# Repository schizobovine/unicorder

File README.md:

# unicorder
Play on the device of Trek fame, just a little bit less capable (only designed to handle a single sensor).

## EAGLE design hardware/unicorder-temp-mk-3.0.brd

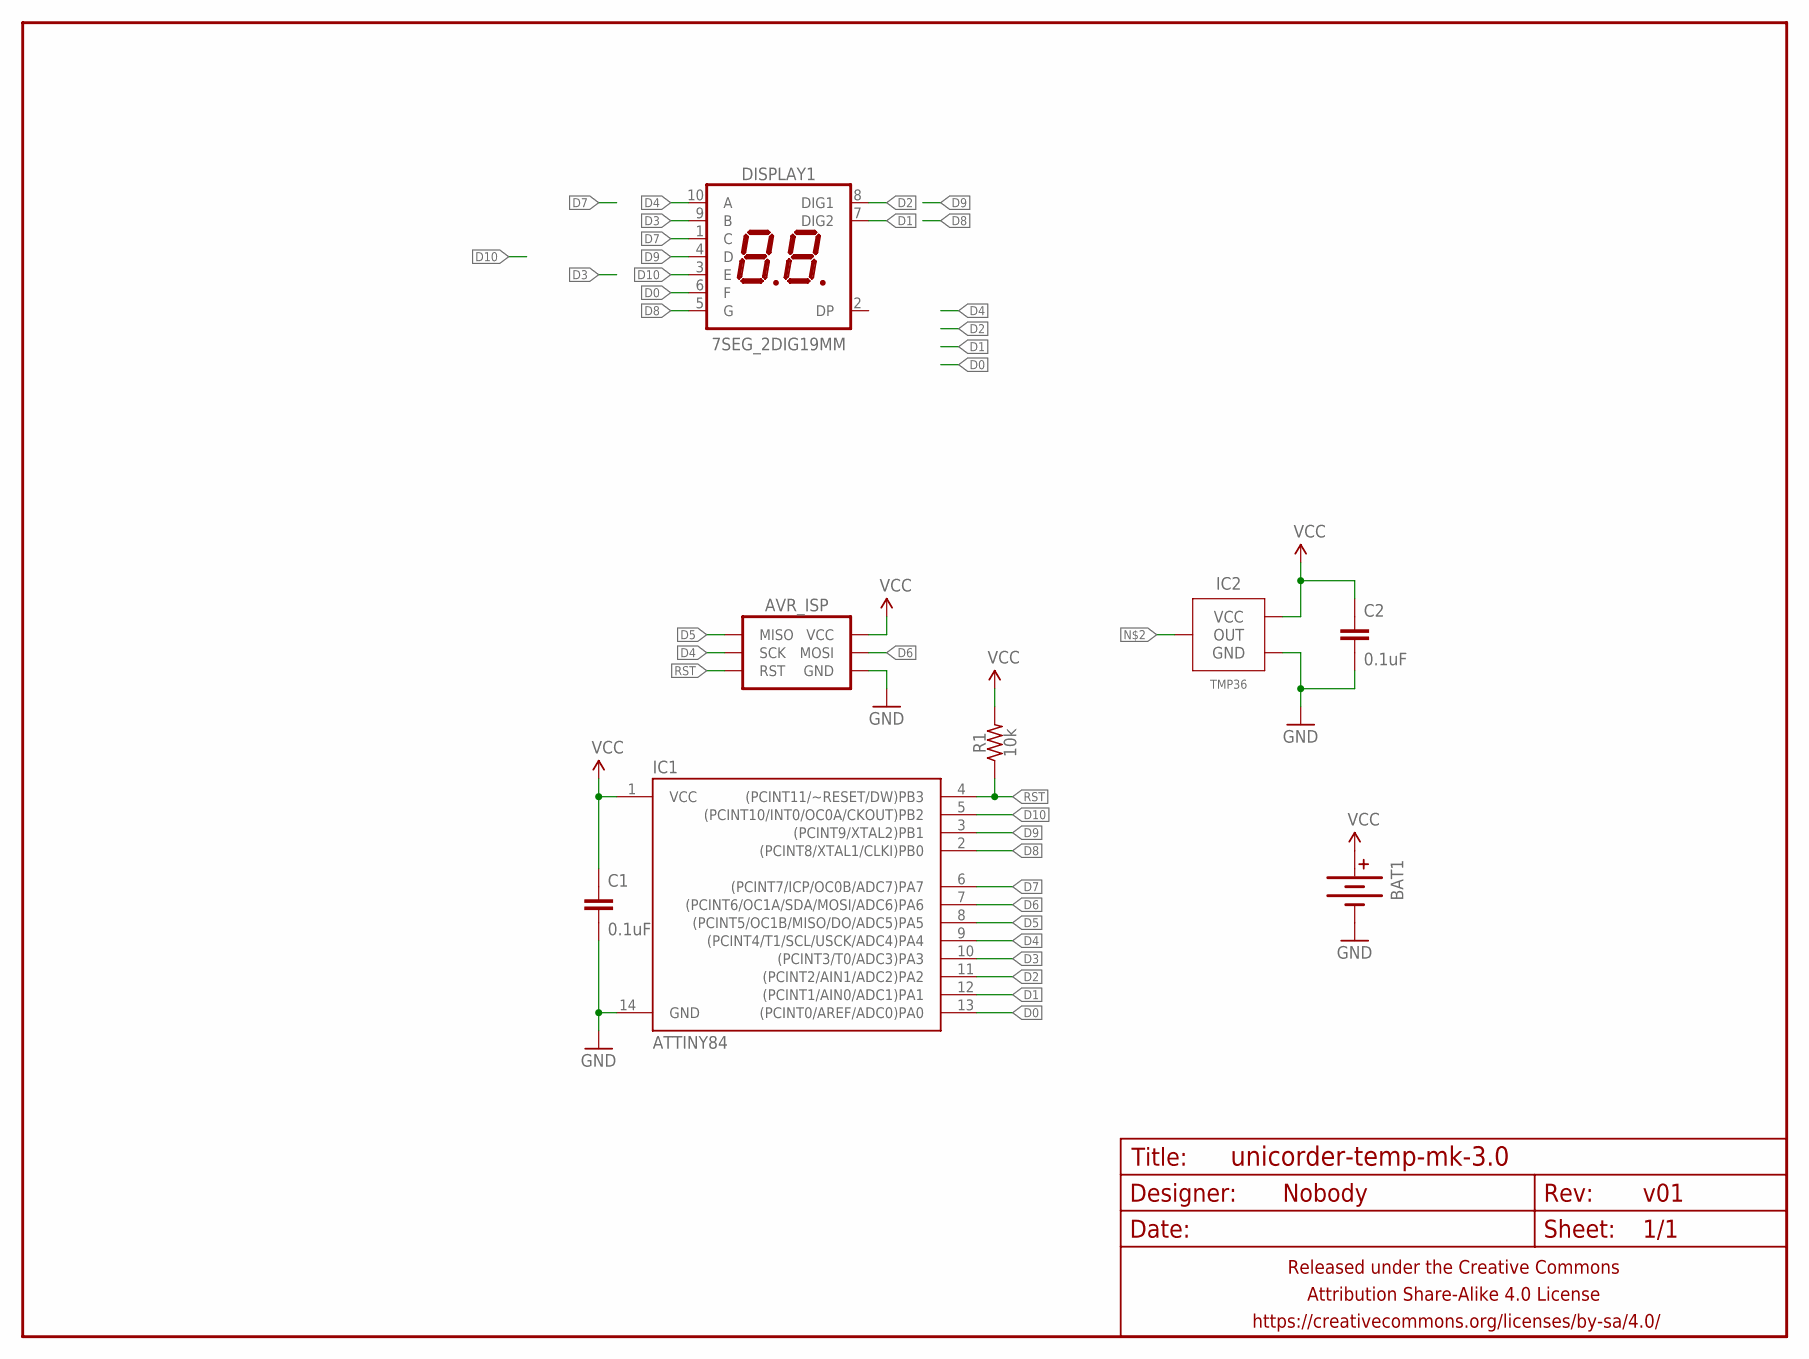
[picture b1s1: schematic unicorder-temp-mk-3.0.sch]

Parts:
AVR_ISP: AVR_SPI_PRG_6SMD_TEST_POINTS; 2X3_SMD_TEST_POINTS
BAT1: BATTERY20PTH_TOPLOAD; BATTCON_20MM_PTH_TOPLOAD
C1: 0.1uF; C0805
C2: 0.1uF; C025-024X044
DISPLAY1: 7SEG_2DIG19MM; 7SEG_2DIG_19MM
FRAME1: FRAME-LETTERNO_PACKAGE; DUMMY
IC1: ATTINY84; SO14
IC2: TMP36; TO-92-AMMO
R1: 10k; R0805

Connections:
D0: DISPLAY1.6 (F), IC1.13 ((PCINT0/AREF/ADC0)PA0)
D1: DISPLAY1.7 (DIG2), IC1.12 ((PCINT1/AIN0/ADC1)PA1)
D2: DISPLAY1.8 (DIG1), IC1.11 ((PCINT2/AIN1/ADC2)PA2)
D3: DISPLAY1.9 (B), IC1.10 ((PCINT3/T0/ADC3)PA3)
D4: AVR_ISP.3 (SCK), DISPLAY1.10 (A), IC1.9 ((PCINT4/T1/SCL/USCK/ADC4)PA4)
D5: AVR_ISP.1 (MISO), IC1.8 ((PCINT5/OC1B/MISO/DO/ADC5)PA5)
D6: AVR_ISP.4 (MOSI), IC1.7 ((PCINT6/OC1A/SDA/MOSI/ADC6)PA6)
D7: DISPLAY1.1 (C), IC1.6 ((PCINT7/ICP/OC0B/ADC7)PA7)
D8: DISPLAY1.5 (G), IC1.2 ((PCINT8/XTAL1/CLKI)PB0)
D9: DISPLAY1.4 (D), IC1.3 ((PCINT9/XTAL2)PB1)
D10: DISPLAY1.3 (E), IC1.5 ((PCINT10/INT0/OC0A/CKOUT)PB2)
GND: AVR_ISP.6 (GND), BAT1.-, C1.2, C2.2, IC1.14 (GND), IC2.3 (GND)
RST: AVR_ISP.5 (RST), IC1.4 ((PCINT11/~RESET/DW)PB3), R1.1
VCC: AVR_ISP.2 (VCC), BAT1.+, C1.1, C2.1, IC1.1 (VCC), IC2.1 (VCC), R1.2

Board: 2 copper layers, 9 parts (6 on the bottom side), 14 nets, no tracks yet.

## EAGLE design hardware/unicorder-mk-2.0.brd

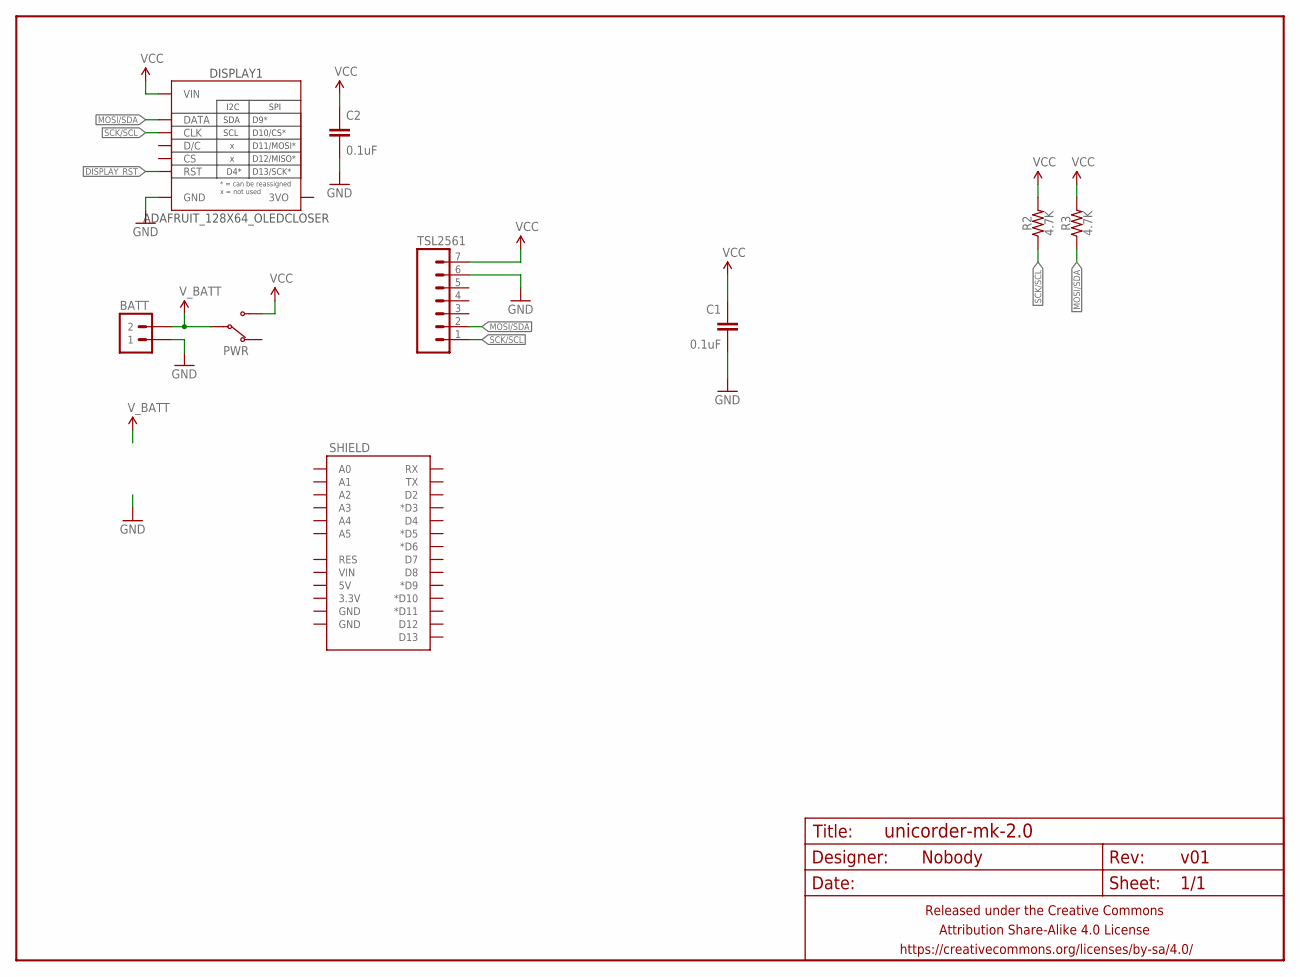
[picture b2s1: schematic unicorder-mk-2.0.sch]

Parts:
BATT: M02JST-PTH-VERT; JST-2-PH-VERT-PTH
C1, C2: 0.1uF; C025-024X044
DISPLAY1: ADAFRUIT_128X64_OLEDCLOSER; ADAFRUIT_128X64_OLED_CLOSER
FRAME1: FRAME-LETTERNO_PACKAGE; DUMMY
PWR: SWITCH-SPDTPTH-RA-2MM; SPDT-RA-2MM
R2, R3: 4.7K; RESISTOR-AXIAL-PTH-5.08MM
SHIELD: ARDUINO_SHIELD_SMALLER; ARDUINO_SHIELD_NOOUTLINE_INSIDE_SMALLER
TSL2561: M07PTH-SLIMASS; 1X07_PTH_SLIMASS

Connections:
DISPLAY_RST: DISPLAY1.RST
GND: BATT.1, C1.2, C2.2, DISPLAY1.GND, TSL2561.6
MOSI/SDA: DISPLAY1.DATA, R3.P$1 (1), TSL2561.2
SCK/SCL: DISPLAY1.CLK, R2.P$1 (1), TSL2561.1
VCC: C1.1, C2.1, DISPLAY1.VIN, PWR.3 (NO), R2.P$2 (2), R3.P$2 (2), TSL2561.7
V_BATT: BATT.2, PWR.2 (COM)

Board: 2 copper layers, 10 parts (1 on the bottom side), 5 nets, no tracks yet.

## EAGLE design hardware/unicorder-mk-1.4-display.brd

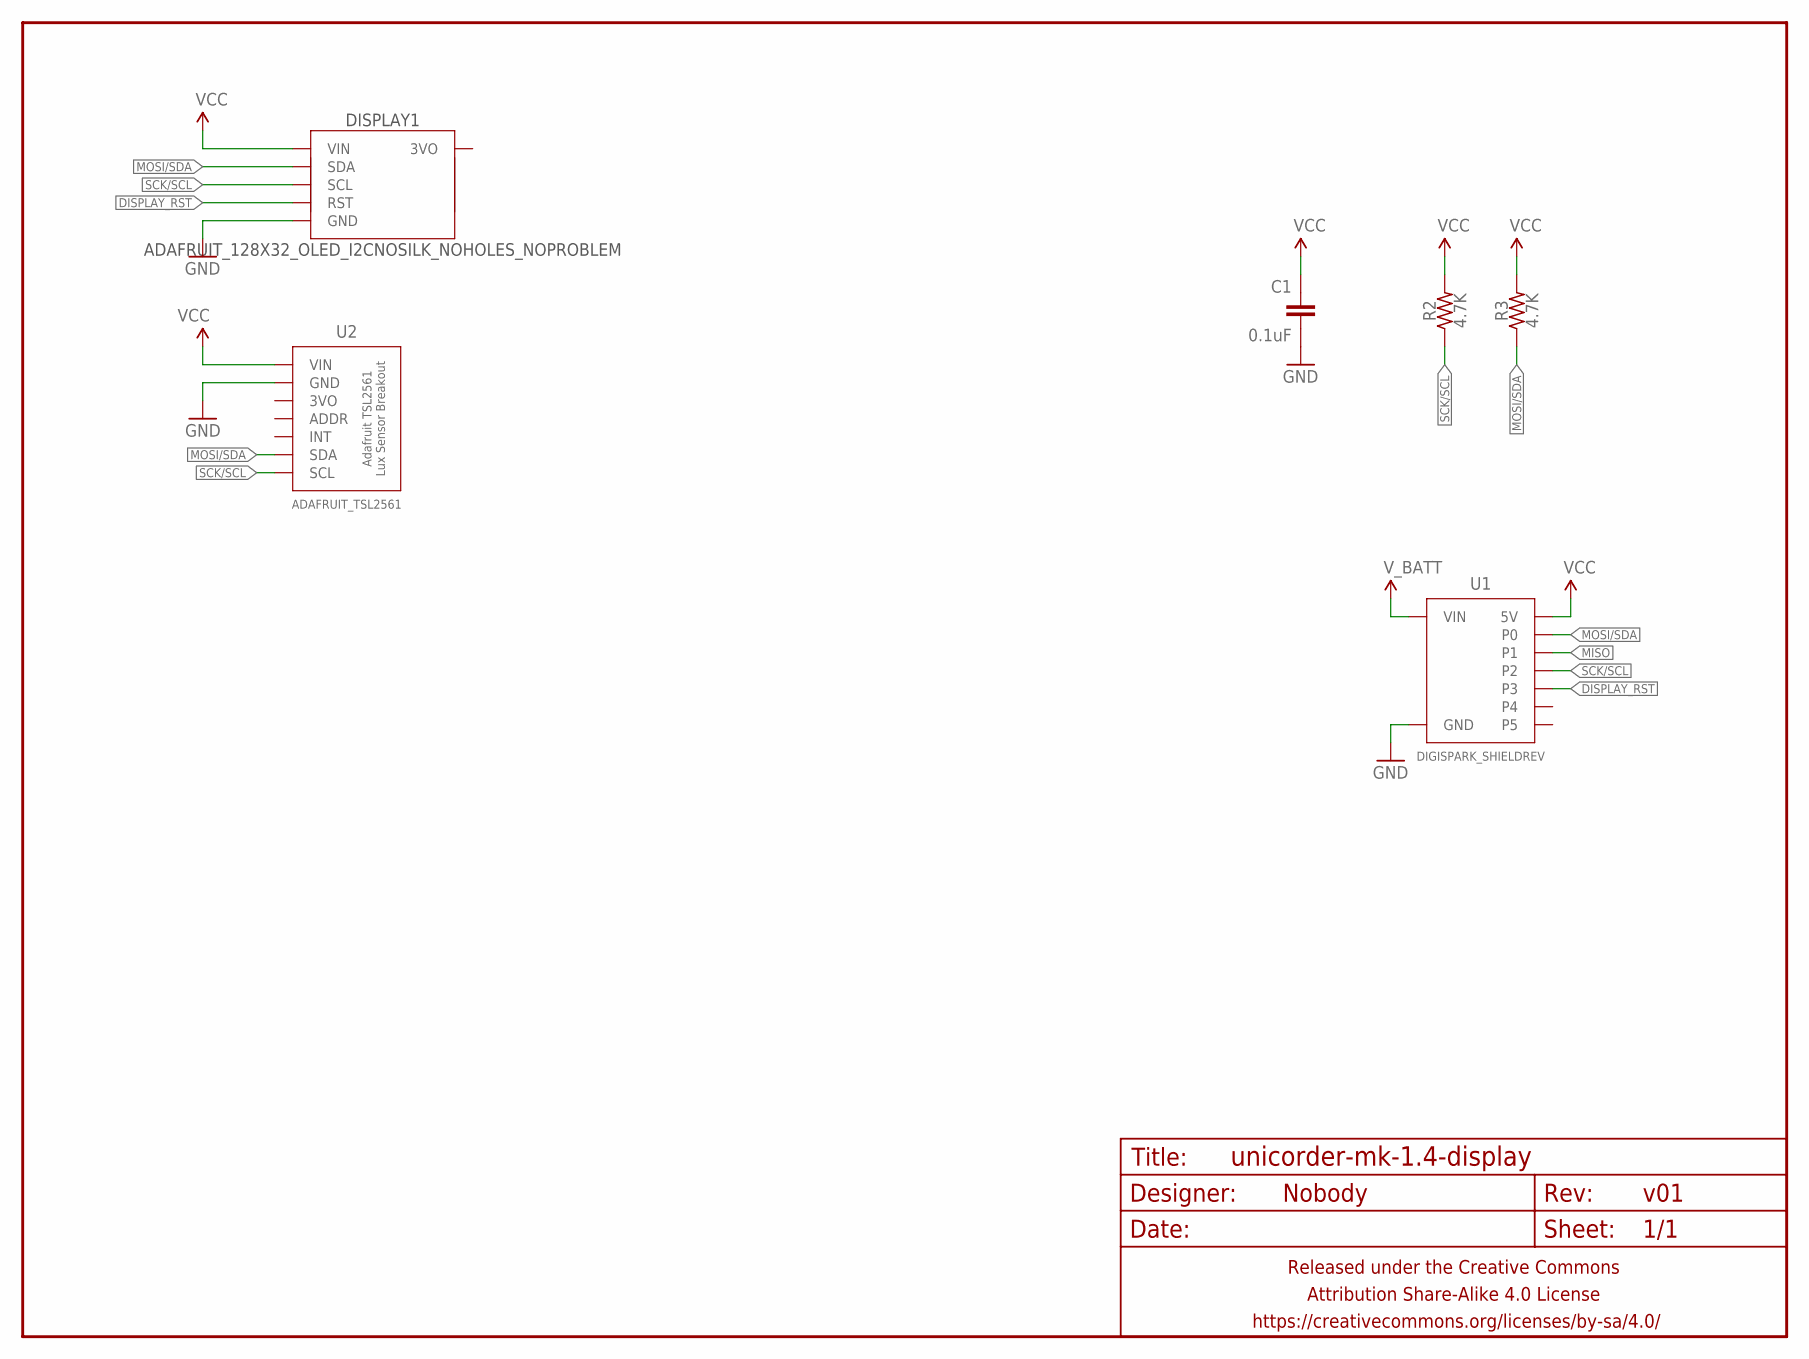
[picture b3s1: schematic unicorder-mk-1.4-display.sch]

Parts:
C1: 0.1uF; C025-024X044
DISPLAY1: ADAFRUIT_128X32_OLED_I2CNOSILK_NOHOLES_NOPROBLEM; ADAFRUIT_128X32_OLED_I2C_CLOSER_NS
FRAME1: FRAME-LETTERNO_PACKAGE; DUMMY
R2, R3: 4.7K; RESISTOR-AXIAL-PTH-7.62MM
U1: DIGISPARK_SHIELDREV; DIGISPARK_SHIELD_REV
U2: ADAFRUIT_TSL2561

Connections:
DISPLAY_RST: DISPLAY1.RST, U1.P3
GND: C1.2, DISPLAY1.GND, U1.GND, U2.GND
MISO: U1.P1
MOSI/SDA: DISPLAY1.SDA, R3.P$1 (1), U1.P0, U2.SDA
SCK/SCL: DISPLAY1.SCL, R2.P$1 (1), U1.P2, U2.SCL
VCC: C1.1, DISPLAY1.VIN, R2.P$2 (2), R3.P$2 (2), U1.5V, U2.VIN
V_BATT: U1.VIN

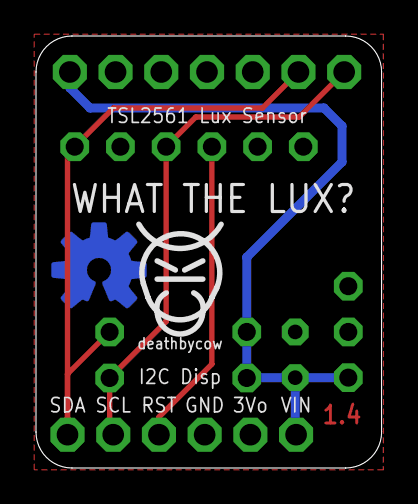
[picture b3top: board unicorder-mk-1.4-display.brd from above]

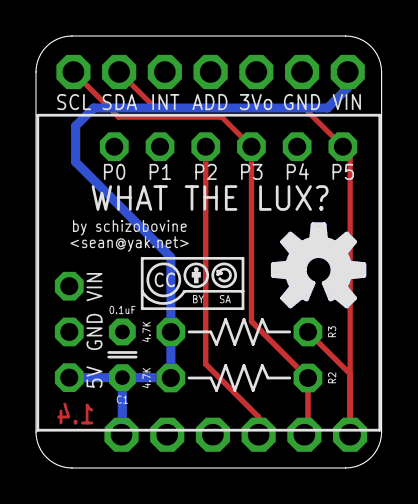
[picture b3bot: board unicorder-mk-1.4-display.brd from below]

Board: 2 copper layers, 19.2 x 24.0 mm, 10 parts (6 on the bottom side), 5 nets.

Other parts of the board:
U$1: CC-BY-SA-4.0-NO-URL
U$2: COW_SMALL
U$3: OSHWLOGO_TOP_0.2

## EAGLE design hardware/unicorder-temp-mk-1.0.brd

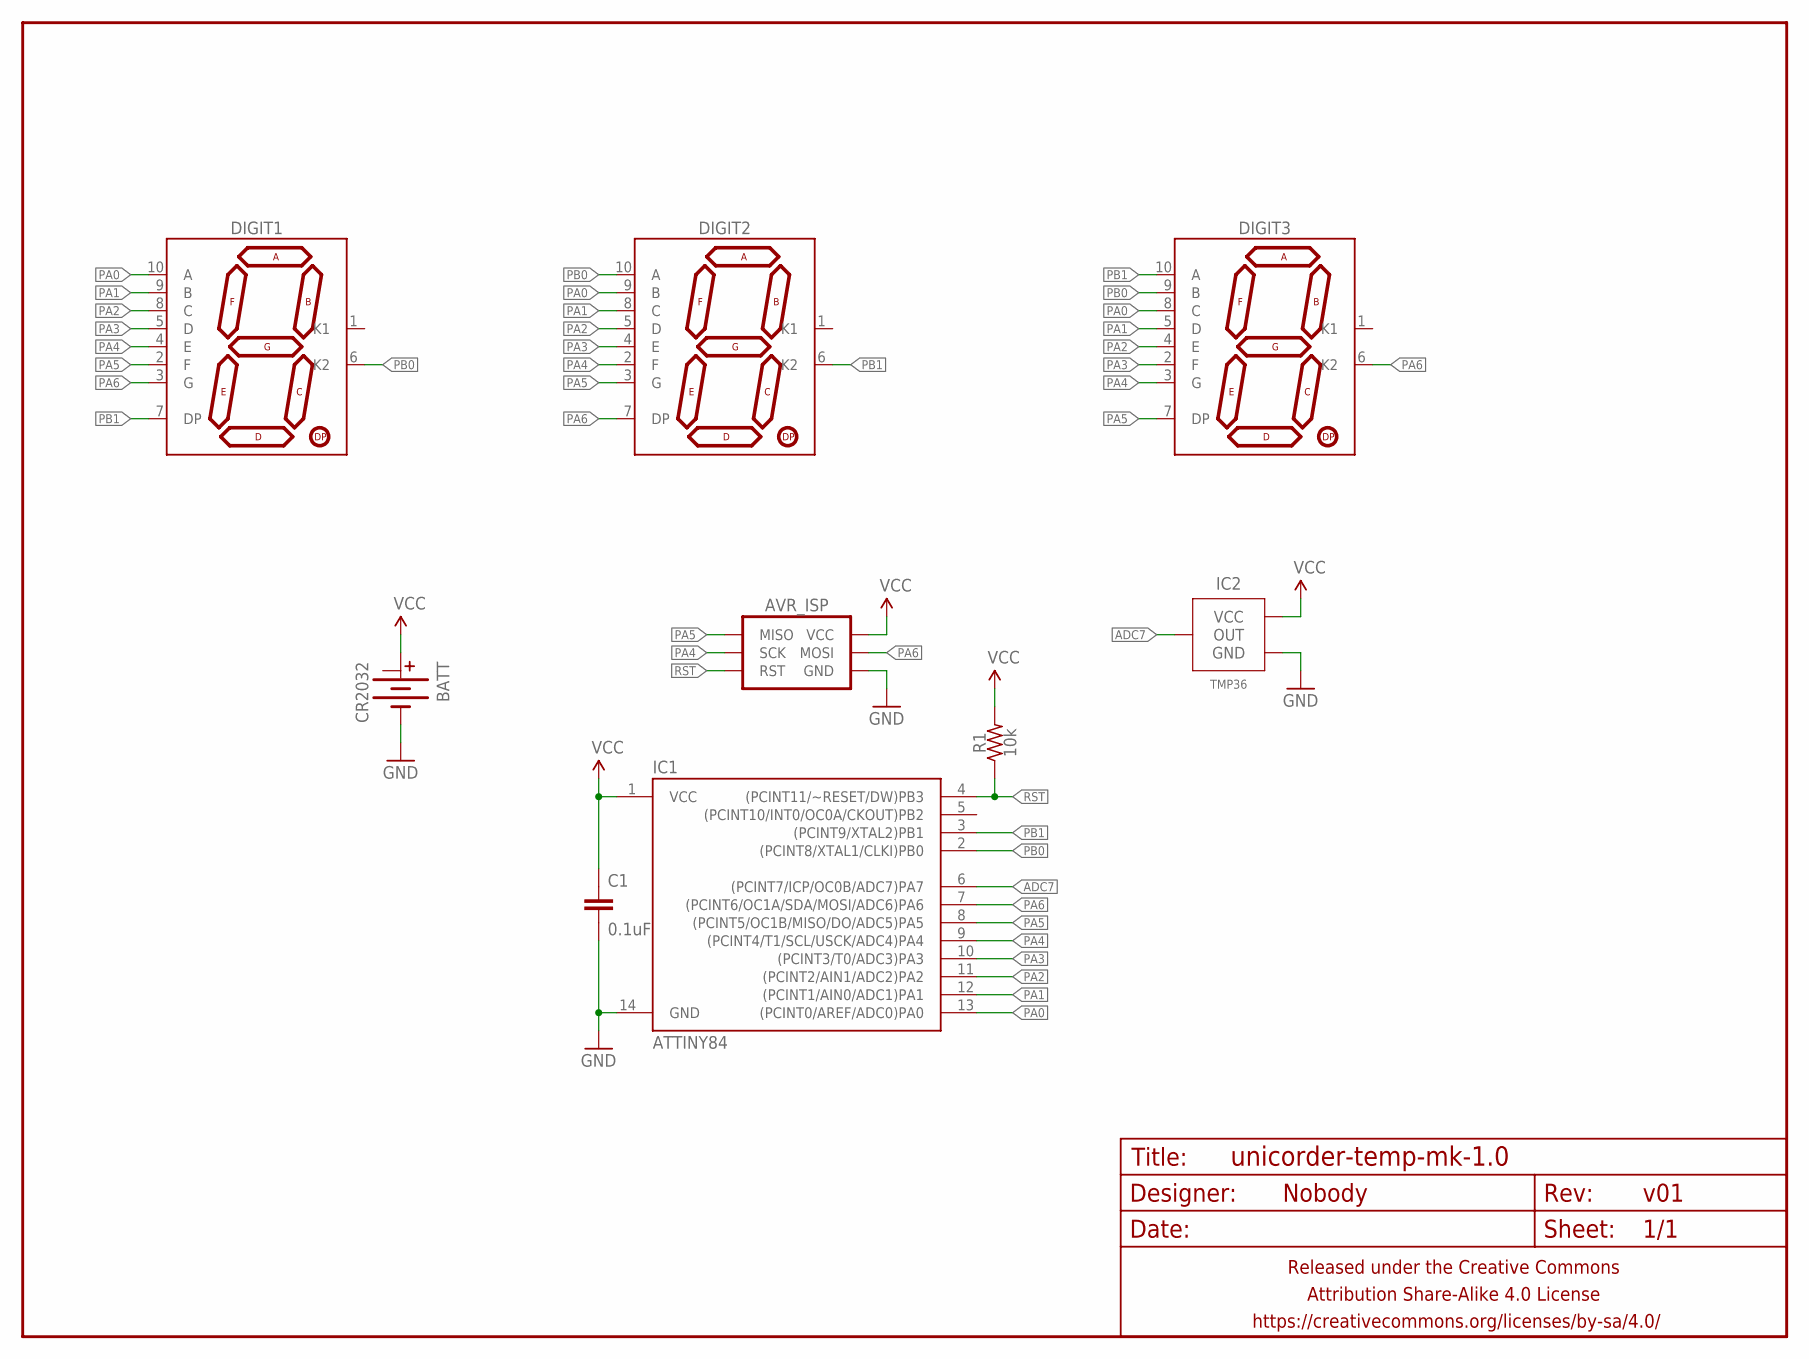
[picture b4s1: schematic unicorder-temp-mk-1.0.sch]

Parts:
AVR_ISP: AVR_SPI_PRG_6PTH; 2X3
BATT: CR2032; BATTCON_20MM_MINE
C1: 0.1uF; C025-024X044
DIGIT1, DIGIT2, DIGIT3: 7SEG_1DIGPTH-10MM; 7SEG_1DIG_10MM
FRAME1: FRAME-LETTERNO_PACKAGE; DUMMY
IC1: ATTINY84; DIL14
IC2: TMP36; TO-92-AMMO
R1: 10k; RESISTOR-AXIAL-PTH-7.62MM

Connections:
ADC7: IC1.6 ((PCINT7/ICP/OC0B/ADC7)PA7), IC2.2 (OUT)
GND: AVR_ISP.6 (GND), BATT.BOTTOM (-), C1.2, IC1.14 (GND), IC2.3 (GND)
PA0: DIGIT1.10 (A), DIGIT2.9 (B), DIGIT3.8 (C), IC1.13 ((PCINT0/AREF/ADC0)PA0)
PA1: DIGIT1.9 (B), DIGIT2.8 (C), DIGIT3.5 (D), IC1.12 ((PCINT1/AIN0/ADC1)PA1)
PA2: DIGIT1.8 (C), DIGIT2.5 (D), DIGIT3.4 (E), IC1.11 ((PCINT2/AIN1/ADC2)PA2)
PA3: DIGIT1.5 (D), DIGIT2.4 (E), DIGIT3.2 (F), IC1.10 ((PCINT3/T0/ADC3)PA3)
PA4: AVR_ISP.3 (SCK), DIGIT1.4 (E), DIGIT2.2 (F), DIGIT3.3 (G), IC1.9 ((PCINT4/T1/SCL/USCK/ADC4)PA4)
PA5: AVR_ISP.1 (MISO), DIGIT1.2 (F), DIGIT2.3 (G), DIGIT3.7 (DP), IC1.8 ((PCINT5/OC1B/MISO/DO/ADC5)PA5)
PA6: AVR_ISP.4 (MOSI), DIGIT1.3 (G), DIGIT2.7 (DP), DIGIT3.6 (K2), IC1.7 ((PCINT6/OC1A/SDA/MOSI/ADC6)PA6)
PB0: DIGIT1.6 (K2), DIGIT2.10 (A), DIGIT3.9 (B), IC1.2 ((PCINT8/XTAL1/CLKI)PB0)
PB1: DIGIT1.7 (DP), DIGIT2.6 (K2), DIGIT3.10 (A), IC1.3 ((PCINT9/XTAL2)PB1)
RST: AVR_ISP.5 (RST), IC1.4 ((PCINT11/~RESET/DW)PB3), R1.P$1 (1)
VCC: AVR_ISP.2 (VCC), BATT.TOP@1 (+), C1.1, IC1.1 (VCC), IC2.1 (VCC), R1.P$2 (2)

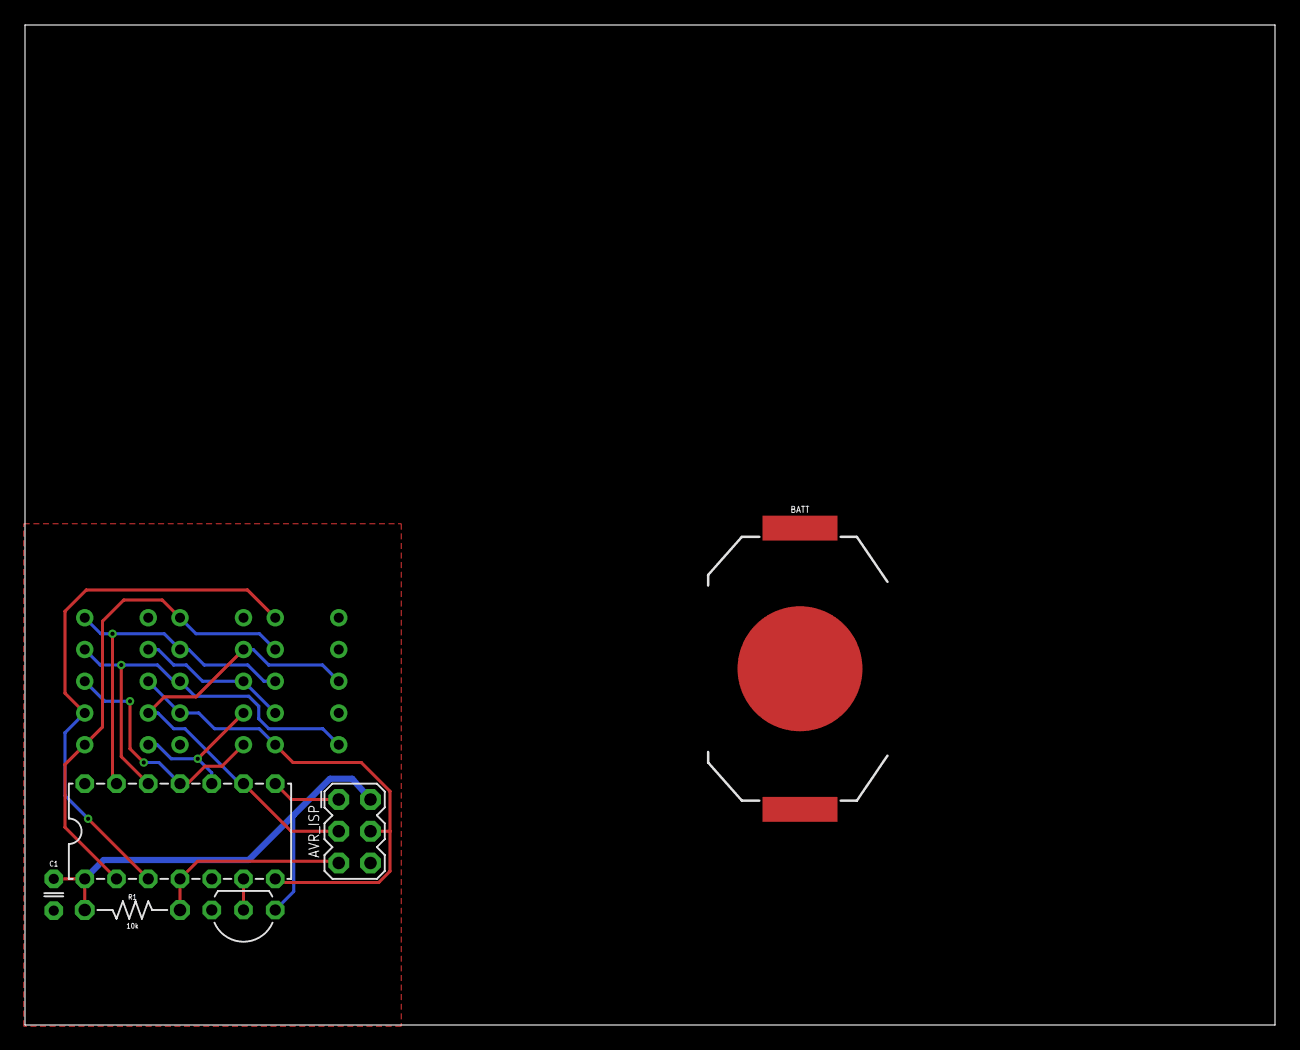
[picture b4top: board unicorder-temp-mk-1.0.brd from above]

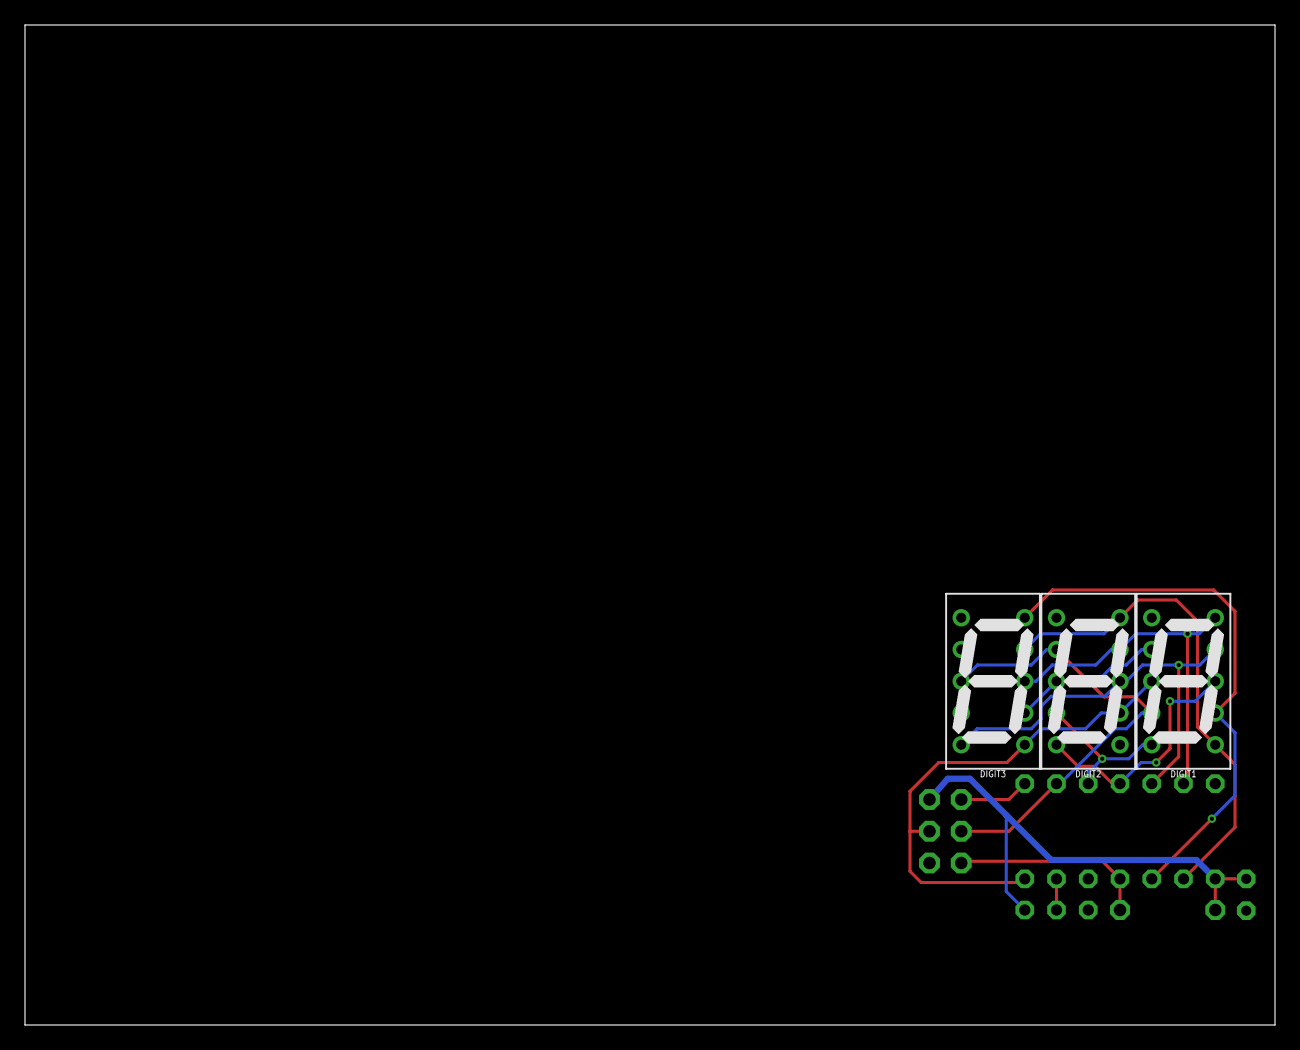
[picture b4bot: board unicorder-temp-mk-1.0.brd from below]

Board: 2 copper layers, 100.0 x 80.0 mm, 10 parts (3 on the bottom side), 13 nets.

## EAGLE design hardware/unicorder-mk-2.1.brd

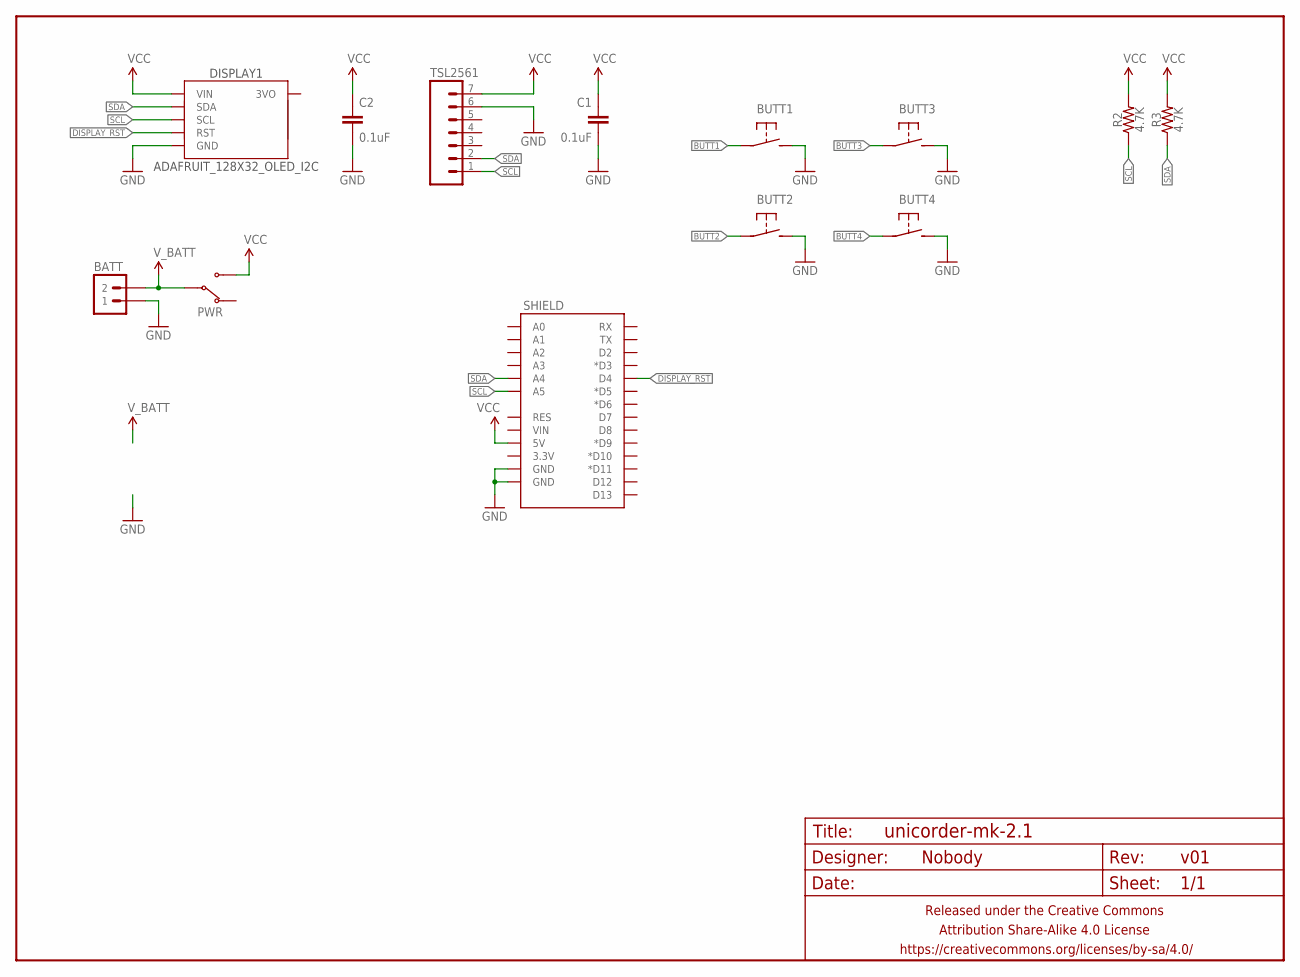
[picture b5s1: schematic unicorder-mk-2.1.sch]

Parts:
BATT: M02JST-PTH-VERT; JST-2-PH-VERT-PTH
BUTT1, BUTT2, BUTT3, BUTT4: SPST-NO-TACT6MM-PTH-SMALL-PADS; DTS-6-SMALL-PADS
C1, C2: 0.1uF; C025-024X044
DISPLAY1: ADAFRUIT_128X32_OLED_I2C; ADAFRUIT_128X32_OLED_I2C_CLOSER
FRAME1: FRAME-LETTERNO_PACKAGE; DUMMY
PWR: SWITCH-SPDTPTH-VERT-2.54MM; SWITCH-SPDT
R2, R3: 4.7K; RESISTOR-AXIAL-PTH-6.35MM
SHIELD: ARDUINO_SHIELD_SMALLER; ARDUINO_SHIELD_NOOUTLINE_INSIDE_SMALLER
TSL2561: M07PTH-SLIMASS; 1X07_PTH_SLIMASS

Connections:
BUTT1: BUTT1.1, BUTT1.2 (1)
BUTT2: BUTT2.1, BUTT2.2 (1)
BUTT3: BUTT3.1, BUTT3.2 (1)
BUTT4: BUTT4.1, BUTT4.2 (1)
DISPLAY_RST: DISPLAY1.RST, SHIELD.D4
GND: BATT.1, BUTT1.3 (2), BUTT1.4 (2), BUTT2.3 (2), BUTT2.4 (2), BUTT3.3 (2), BUTT3.4 (2), BUTT4.3 (2), BUTT4.4 (2), C1.2, C2.2, DISPLAY1.GND, SHIELD.GND@0 (GND), SHIELD.GND@1 (GND), TSL2561.6
SCL: DISPLAY1.SCL, R2.P$1 (1), SHIELD.A5, TSL2561.1
SDA: DISPLAY1.SDA, R3.P$1 (1), SHIELD.A4, TSL2561.2
VCC: C1.1, C2.1, DISPLAY1.VIN, PWR.3 (NO), R2.P$2 (2), R3.P$2 (2), SHIELD.5V, TSL2561.7
V_BATT: BATT.2, PWR.2 (COM)

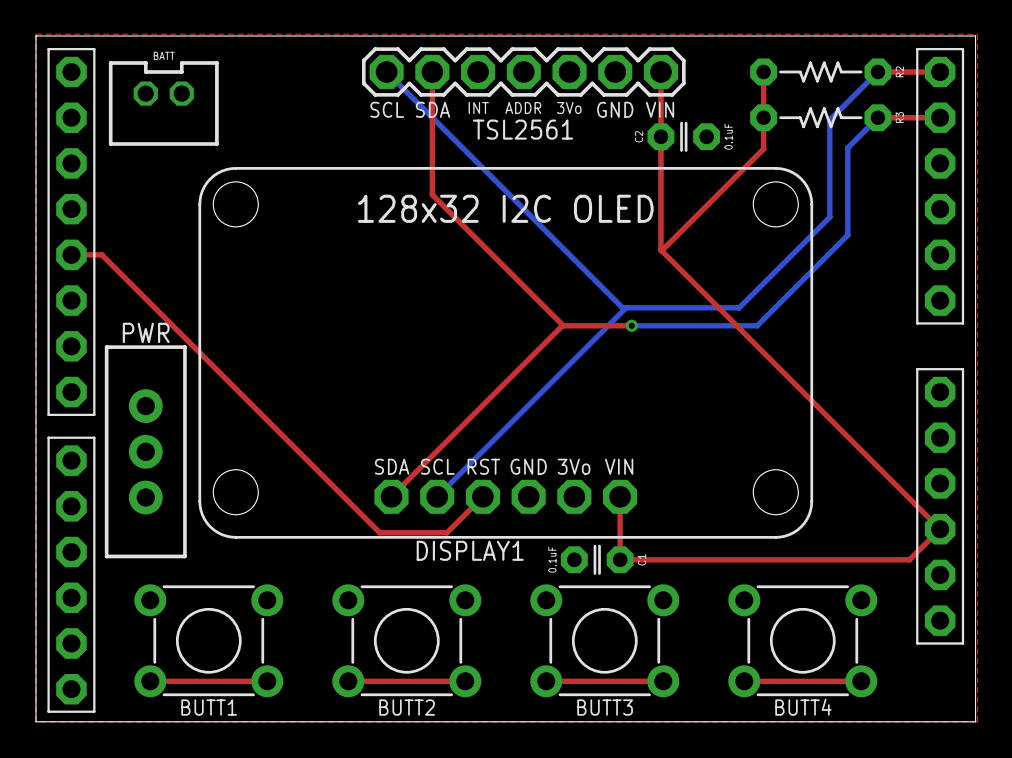
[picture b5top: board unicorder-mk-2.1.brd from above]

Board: 2 copper layers, 52.2 x 38.1 mm, 14 parts (0 on the bottom side), 10 nets.

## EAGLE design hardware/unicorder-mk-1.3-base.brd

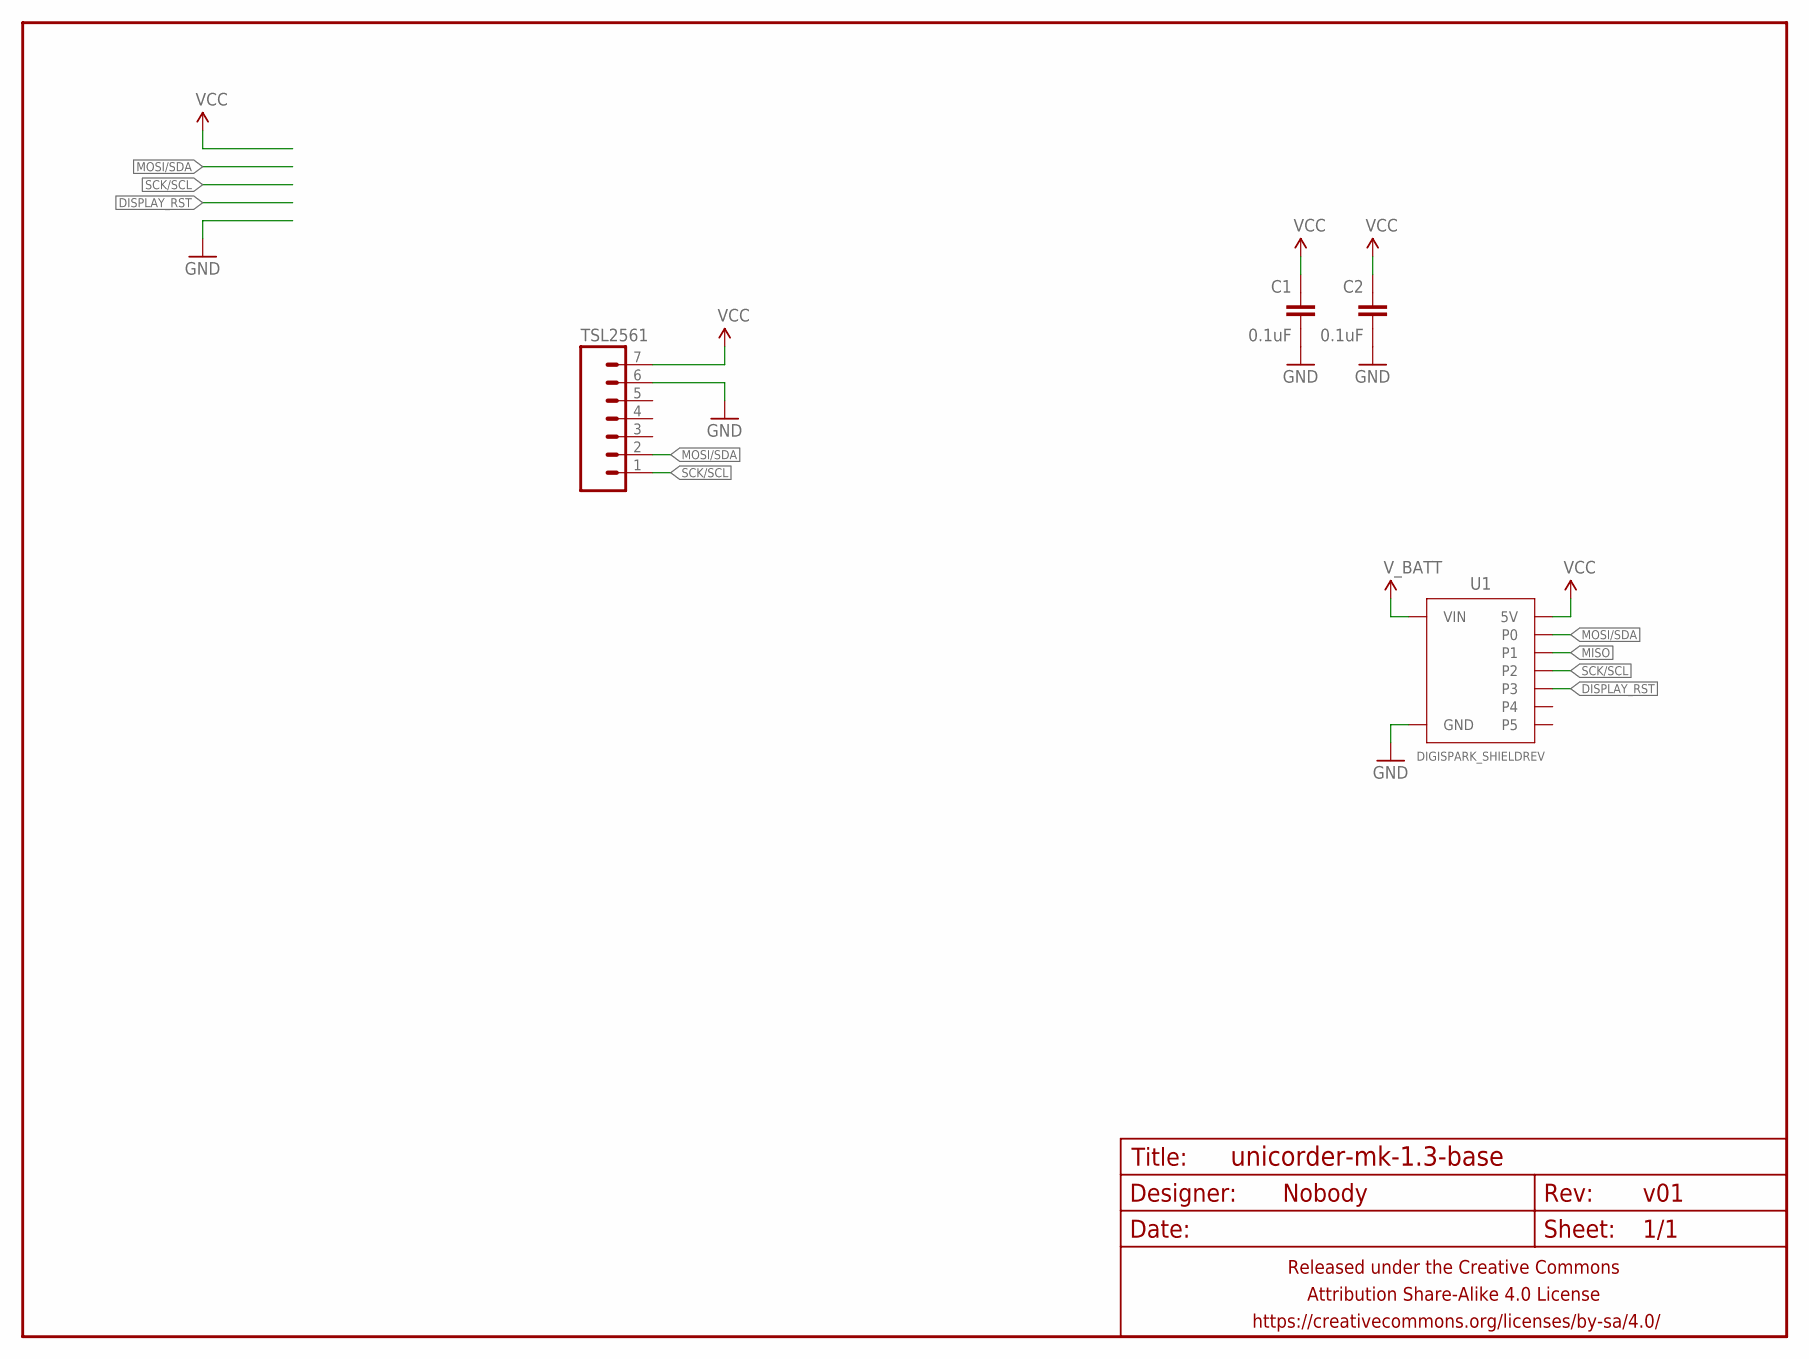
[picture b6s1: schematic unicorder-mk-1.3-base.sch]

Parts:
C1, C2: 0.1uF; C025-024X044
FRAME1: FRAME-LETTERNO_PACKAGE; DUMMY
TSL2561: M07PTH-SLIMASS; 1X07_PTH_SLIMASS
U1: DIGISPARK_SHIELDREV; DIGISPARK_SHIELD_REV

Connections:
DISPLAY_RST: U1.P3
GND: C1.2, C2.2, TSL2561.6, U1.GND
MISO: U1.P1
MOSI/SDA: TSL2561.2, U1.P0
SCK/SCL: TSL2561.1, U1.P2
VCC: C1.1, C2.1, TSL2561.7, U1.5V
V_BATT: U1.VIN

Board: 2 copper layers, 5 parts (4 on the bottom side), 4 nets, no tracks yet.

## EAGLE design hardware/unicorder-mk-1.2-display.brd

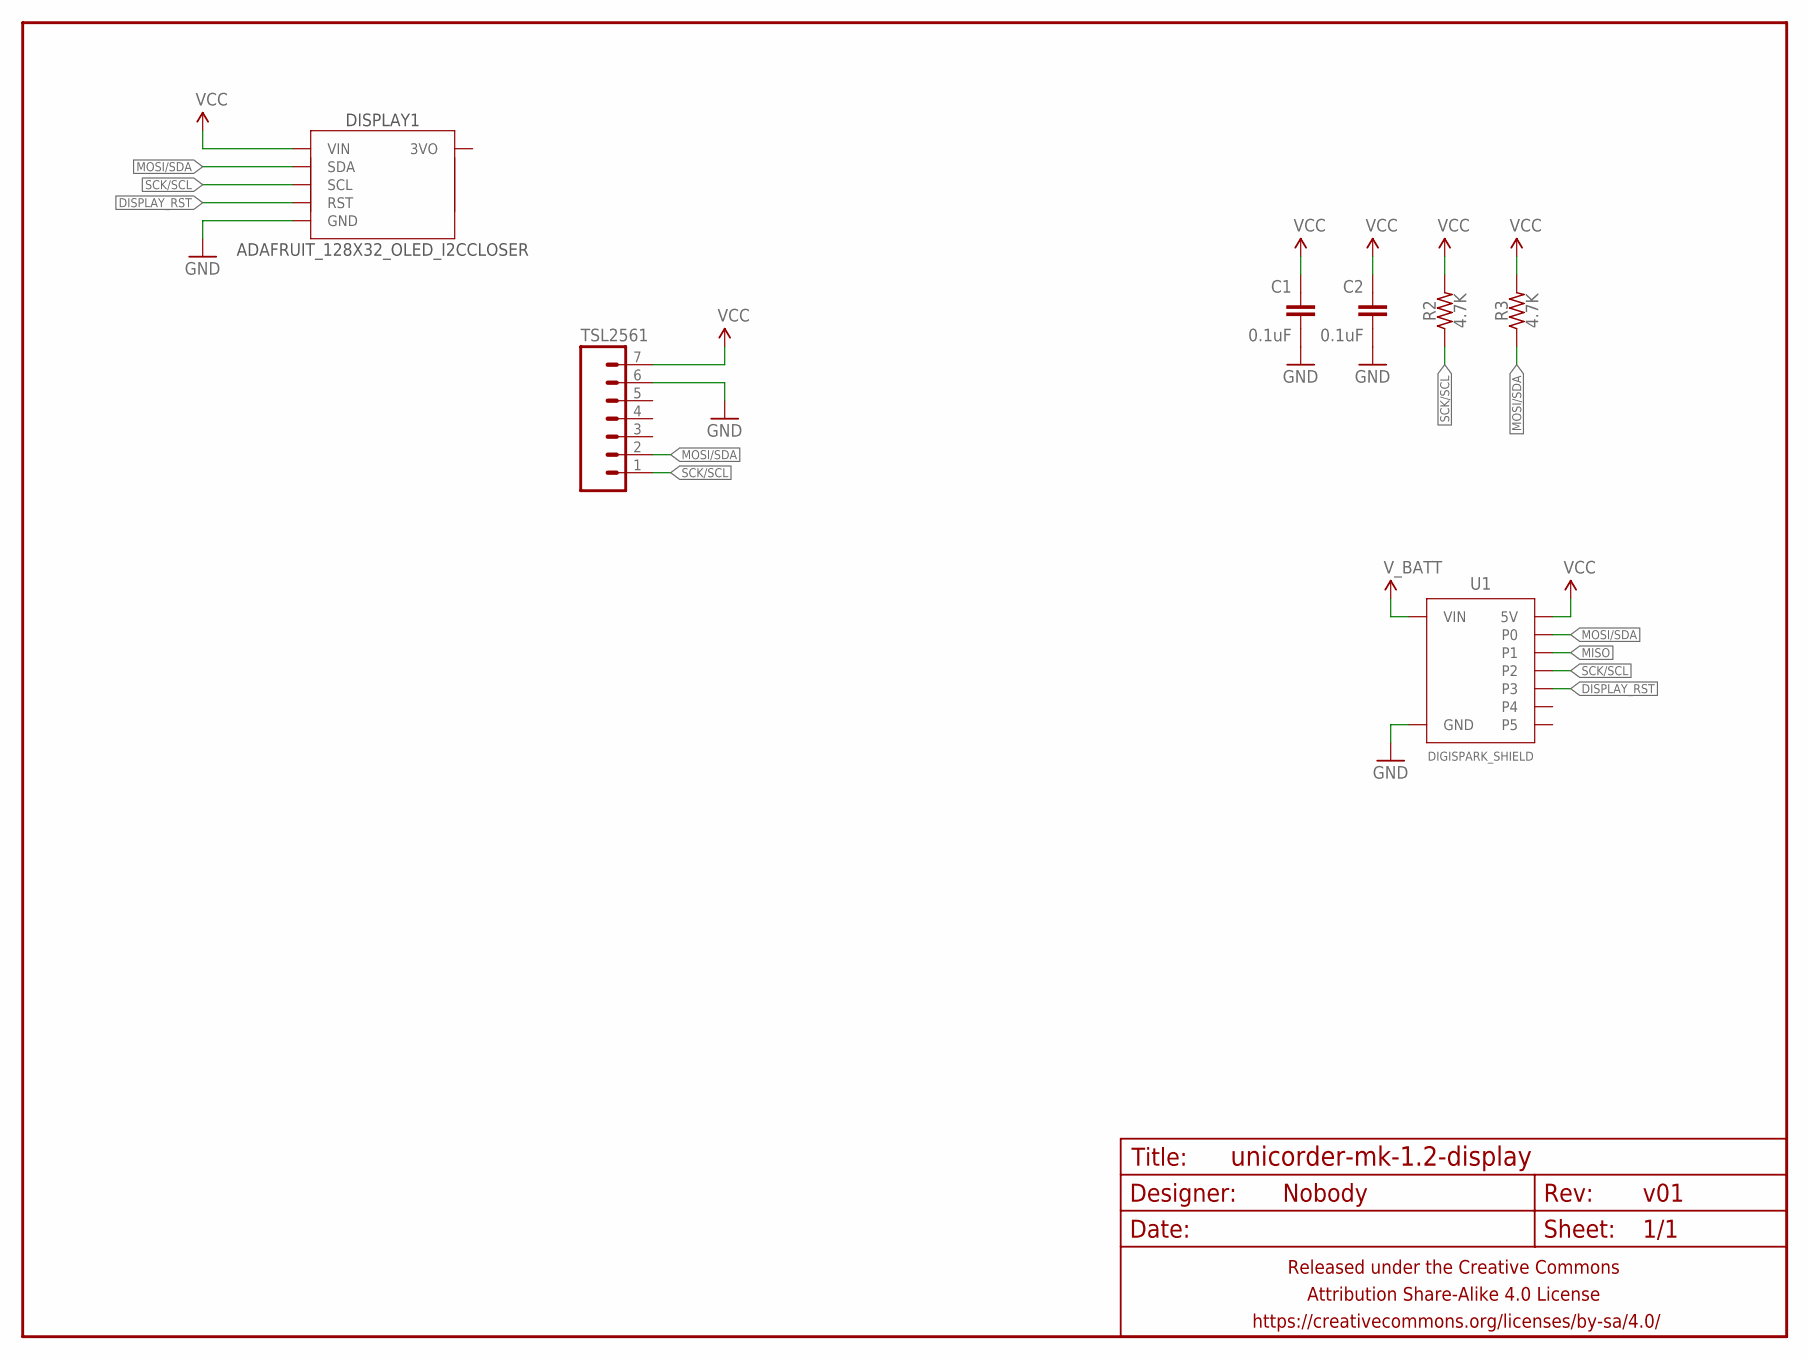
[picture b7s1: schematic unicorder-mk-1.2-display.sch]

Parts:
C1, C2: 0.1uF; C025-024X044
DISPLAY1: ADAFRUIT_128X32_OLED_I2CCLOSER; ADAFRUIT_128X32_OLED_I2C_CLOSER
FRAME1: FRAME-LETTERNO_PACKAGE; DUMMY
R2, R3: 4.7K; RESISTOR-AXIAL-PTH-7.62MM
TSL2561: M07PTH-SLIMASS; 1X07_PTH_SLIMASS
U1: DIGISPARK_SHIELD

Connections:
DISPLAY_RST: DISPLAY1.RST, U1.P3
GND: C1.2, C2.2, DISPLAY1.GND, TSL2561.6, U1.GND
MISO: U1.P1
MOSI/SDA: DISPLAY1.SDA, R3.P$1 (1), TSL2561.2, U1.P0
SCK/SCL: DISPLAY1.SCL, R2.P$1 (1), TSL2561.1, U1.P2
VCC: C1.1, C2.1, DISPLAY1.VIN, R2.P$2 (2), R3.P$2 (2), TSL2561.7, U1.5V
V_BATT: U1.VIN

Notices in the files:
parts and their libraries:
A_butts: Released under the Creative Commons Attribution Share-Alike 4.0 License
A_butts: https://creativecommons.org/licenses/by-sa/4.0
A_butts: Released under the Creative Commons
